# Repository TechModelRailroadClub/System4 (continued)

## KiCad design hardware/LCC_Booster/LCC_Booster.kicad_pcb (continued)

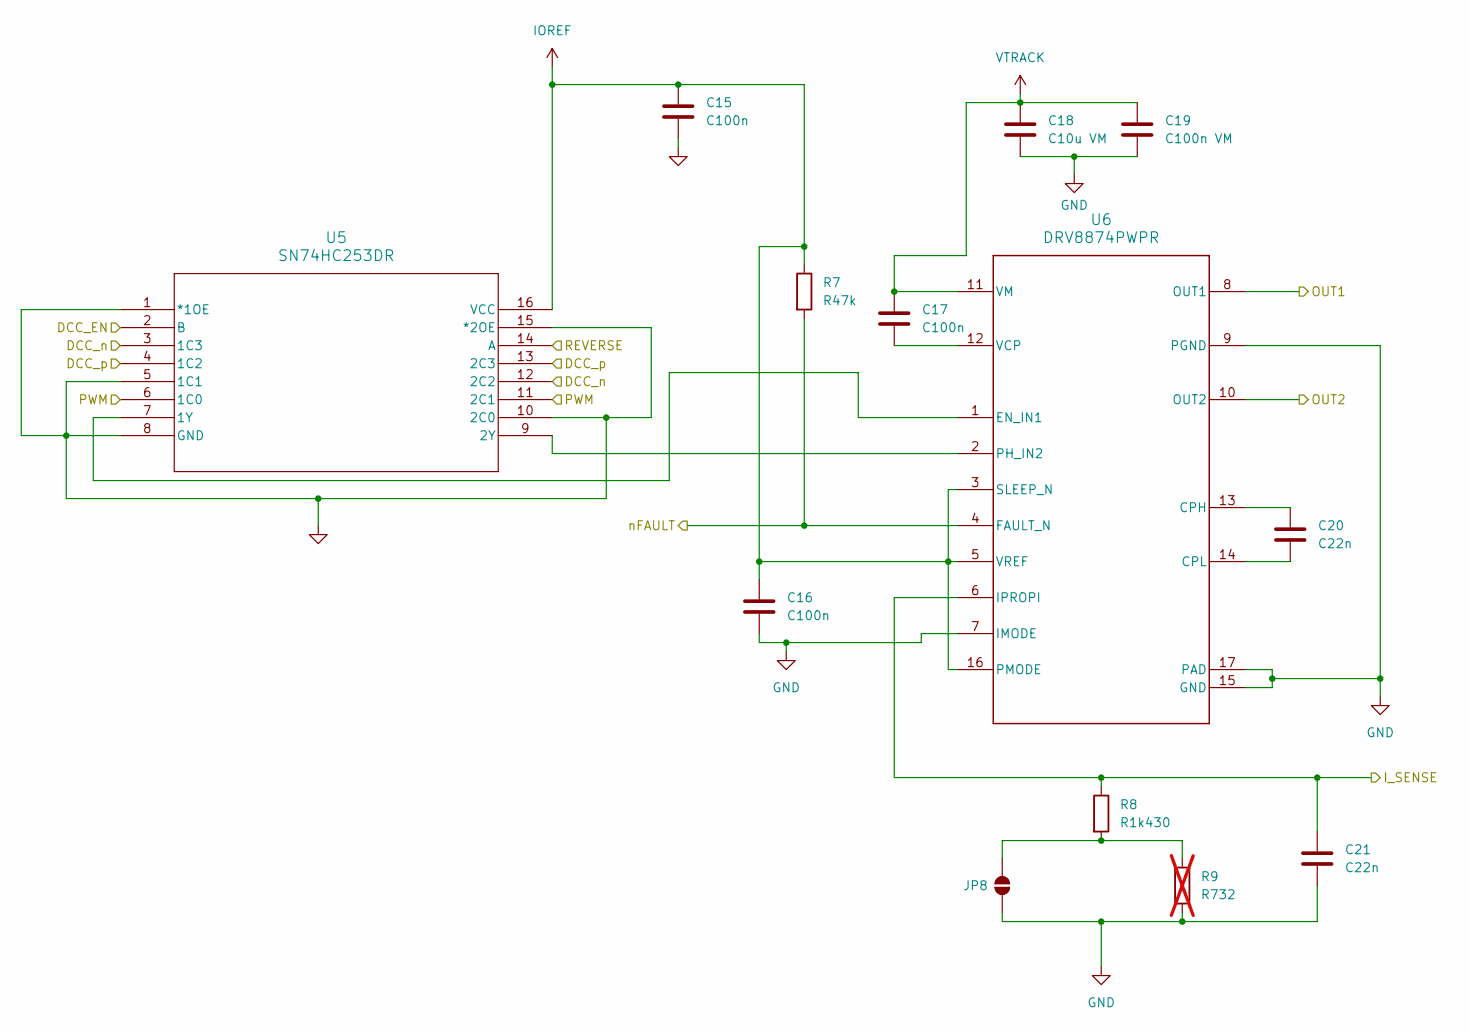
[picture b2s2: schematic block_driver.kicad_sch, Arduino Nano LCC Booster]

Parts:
C15, C16, C17: C100n; C_0805_2012Metric_Pad1.18x1.45mm_HandSolder; Manufacturer Part Number CL21B104KACNFNC
C18: C10u VM; C_1206_3216Metric_Pad1.33x1.80mm_HandSolder; Manufacturer Part Number CL31A106KBHNNNE
C19: C100n VM; C_0805_2012Metric_Pad1.18x1.45mm_HandSolder; Manufacturer Part Number CL21B104KBFXPJE
C20, C21: C22n; C_0805_2012Metric_Pad1.18x1.45mm_HandSolder; Manufacturer Part Number CL21B223JBANNNC
JP8: SolderJumper_2; SolderJumper-2_P1.3mm_Open_RoundedPad1.0x1.5mm
R7: R47k; R_0805_2012Metric_Pad1.20x1.40mm_HandSolder; Manufacturer Part Number ERJ6ENF4702V
R8: R1k430; R_0805_2012Metric_Pad1.20x1.40mm_HandSolder; Manufacturer Part Number RC0805FR-071K43L
R9: R732; R_0805_2012Metric_Pad1.20x1.40mm_HandSolder; not fitted
U5: SN74HC253DR; SO-16_3.9x9.9mm_P1.27mm; Manufacturer Part Number SN74HC253DR
U6: DRV8874PWPR; PWP0016J_NV; Manufacturer Part Number DRV8874PWPR

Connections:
/dcc_en_C: U5.2 (B); also elsewhere on the board
/dcc_n: U5.3 (1C3), U5.12 (2C2); also elsewhere on the board
/dcc_p: U5.4 (1C2), U5.13 (2C3); also elsewhere on the board
/dir_C: U5.14 (A); also elsewhere on the board
/nFault_C: R7.2, U6.4 (FAULT_N); also elsewhere on the board
/out1_C: U6.8 (OUT1); also elsewhere on the board
/out2_C: U6.10 (OUT2); also elsewhere on the board
/pwm_C: U5.6 (1C0), U5.11 (2C1); also elsewhere on the board
/sense_C: C21.1, R8.1, U6.6 (IPROPI); also elsewhere on the board
GND: C15.2, C16.2, C18.2, C19.2, C21.2, JP8.1 (A), R9.2, U5.1 (*1OE), U5.5 (1C1), U5.8 (GND), U5.10 (2C0), U5.15 (*2OE), U6.7 (IMODE), U6.9 (PGND), U6.15 (GND), U6.17 (PAD); also elsewhere on the board
IOREF: C15.1, C16.1, R7.1, U5.16 (VCC), U6.3 (SLEEP_N), U6.5 (VREF), U6.16 (PMODE); also elsewhere on the board
unnamed: JP8.2 (B), R8.2, R9.1
unnamed: U5.7 (1Y), U6.1 (EN_IN1)
unnamed: U5.9 (2Y), U6.2 (PH_IN2)
unnamed: C20.1, U6.13 (CPH)
unnamed: C20.2, U6.14 (CPL)
unnamed: C17.2, U6.12 (VCP)
VTRACK: C17.1, C18.1, C19.1, U6.11 (VM); also elsewhere on the board

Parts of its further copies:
C1, C2, C3, C10, C22, C23, C24: C100n; C_0805_2012Metric_Pad1.18x1.45mm_HandSolder; Manufacturer Part Number CL21B104KACNFNC
C4, C11, C25: C10u VM; C_1206_3216Metric_Pad1.33x1.80mm_HandSolder; Manufacturer Part Number CL31A106KBHNNNE
C5, C12: C100n VM; C_0805_2012Metric_Pad1.18x1.45mm_HandSolder; Manufacturer Part Number CL21B104KBFXPJE
C7, C13, C14, C27, C28: C22n; C_0805_2012Metric_Pad1.18x1.45mm_HandSolder; Manufacturer Part Number CL21B223JBANNNC
JP6, JP7, JP9: SolderJumper_2; SolderJumper-2_P1.3mm_Open_RoundedPad1.0x1.5mm
R1, R4: R47k; R_0805_2012Metric_Pad1.20x1.40mm_HandSolder; Manufacturer Part Number ERJ6ENF4702V
R2: R1k430; R_0805_2012Metric_Pad1.20x1.40mm_HandSolder; Manufacturer Part Number RC0805FR-071K43L
R3, R6, R12: R732; R_0805_2012Metric_Pad1.20x1.40mm_HandSolder; not fitted
U1, U3, U7: SN74HC253DR; SO-16_3.9x9.9mm_P1.27mm; Manufacturer Part Number SN74HC253DR
U2, U4, U8: DRV8874PWPR; PWP0016J_NV; Manufacturer Part Number DRV8874PWPR

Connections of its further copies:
/dcc_en_A: U1.2 (B); also elsewhere on the board
/dcc_en_B: U3.2 (B); also elsewhere on the board
/dcc_en_D: U7.2 (B); also elsewhere on the board
/dcc_n: U1.3 (1C3), U1.12 (2C2), U3.3 (1C3), U3.12 (2C2), U7.3 (1C3), U7.12 (2C2); also elsewhere on the board
/dcc_p: U1.4 (1C2), U1.13 (2C3), U3.4 (1C2), U3.13 (2C3), U7.4 (1C2), U7.13 (2C3); also elsewhere on the board
/dir_A: U1.14 (A); also elsewhere on the board
/dir_B: U3.14 (A); also elsewhere on the board
/dir_D: U7.14 (A); also elsewhere on the board
/nFault_A: R1.2, U2.4 (FAULT_N); also elsewhere on the board
/nFault_B: R4.2, U4.4 (FAULT_N); also elsewhere on the board
/nFault_C: U8.4 (FAULT_N); also elsewhere on the board
/out1_A: U2.8 (OUT1); also elsewhere on the board
/out1_B: U4.8 (OUT1); also elsewhere on the board
/out1_D: U8.8 (OUT1); also elsewhere on the board
/out2_A: U2.10 (OUT2); also elsewhere on the board
/out2_B: U4.10 (OUT2); also elsewhere on the board
/out2_D: U8.10 (OUT2); also elsewhere on the board
/pwm_A: U1.6 (1C0), U1.11 (2C1); also elsewhere on the board
/pwm_B: U3.6 (1C0), U3.11 (2C1); also elsewhere on the board
/pwm_D: U7.6 (1C0), U7.11 (2C1); also elsewhere on the board
/sense_A: C7.1, R2.1, U2.6 (IPROPI); also elsewhere on the board
/sense_B: C14.1, U4.6 (IPROPI); also elsewhere on the board
/sense_D: C28.1, U8.6 (IPROPI); also elsewhere on the board
GND: C1.2, C2.2, C4.2, C5.2, C7.2, C11.2, C12.2, C14.2, C22.2, C23.2, C25.2, C28.2, JP6.1 (A), JP7.1 (A), JP9.1 (A), R3.2, R6.2, R12.2, U1.1 (*1OE), U1.5 (1C1), U1.8 (GND), U1.10 (2C0), U1.15 (*2OE), U2.7 (IMODE), U2.9 (PGND), U2.15 (GND), U2.17 (PAD), U3.1 (*1OE), U3.5 (1C1), U3.8 (GND), U3.10 (2C0), U3.15 (*2OE), U4.7 (IMODE), U4.9 (PGND), U4.15 (GND), U4.17 (PAD), U7.1 (*1OE), U7.5 (1C1), U7.8 (GND), U7.10 (2C0), U7.15 (*2OE), U8.7 (IMODE), U8.9 (PGND), U8.15 (GND), U8.17 (PAD); also elsewhere on the board
IOREF: C1.1, C2.1, C22.1, C23.1, R1.1, R4.1, U1.16 (VCC), U2.3 (SLEEP_N), U2.5 (VREF), U2.16 (PMODE), U3.16 (VCC), U4.3 (SLEEP_N), U4.5 (VREF), U4.16 (PMODE), U7.16 (VCC), U8.3 (SLEEP_N), U8.5 (VREF), U8.16 (PMODE); also elsewhere on the board
unnamed: JP6.2 (B), R2.2, R3.1
unnamed 47: JP7.2 (B), R6.1; also elsewhere on the board
unnamed 49: JP9.2 (B), R12.1; also elsewhere on the board
unnamed: U1.7 (1Y), U2.1 (EN_IN1)
unnamed: U1.9 (2Y), U2.2 (PH_IN2)
unnamed 56: U2.13 (CPH); also elsewhere on the board
unnamed 57: U2.14 (CPL); also elsewhere on the board
unnamed: C3.2, U2.12 (VCP)
unnamed: U3.7 (1Y), U4.1 (EN_IN1)
unnamed: U3.9 (2Y), U4.2 (PH_IN2)
unnamed: C13.1, U4.13 (CPH)
unnamed: C13.2, U4.14 (CPL)
unnamed: C10.2, U4.12 (VCP)
unnamed: U7.7 (1Y), U8.1 (EN_IN1)
unnamed: U7.9 (2Y), U8.2 (PH_IN2)
unnamed: C27.1, U8.13 (CPH)
unnamed: C27.2, U8.14 (CPL)
unnamed: C24.2, U8.12 (VCP)
VTRACK: C3.1, C4.1, C5.1, C10.1, C11.1, C12.1, C24.1, C25.1, U2.11 (VM), U4.11 (VM), U8.11 (VM); also elsewhere on the board

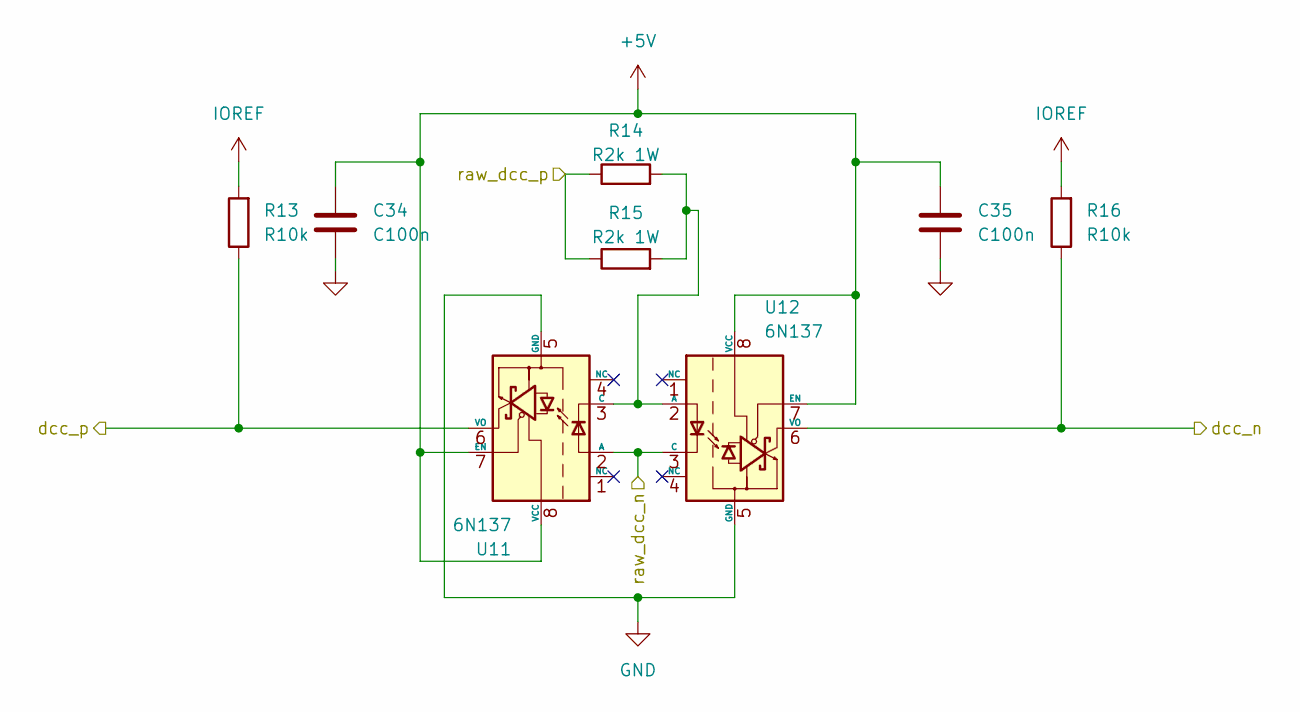
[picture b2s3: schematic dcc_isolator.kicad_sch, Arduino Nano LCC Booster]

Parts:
C34, C35: C100n; C_0805_2012Metric_Pad1.18x1.45mm_HandSolder; Manufacturer Part Number CL21B104KACNFNC
R13, R16: R10k; R_0805_2012Metric_Pad1.20x1.40mm_HandSolder; Manufacturer Part Number RC0805JR-0710KL
R14, R15: R2k 1W; R_2512_6332Metric_Pad1.40x3.35mm_HandSolder; Manufacturer Part Number AC2512JK-072KL
U11, U12: 6N137; DIP-8_W7.62mm_SMDSocket_SmallPads; Manufacturer Part Number 6N137S-TA1-L

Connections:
+5V: C34.1, C35.1, U11.7 (EN), U11.8 (VCC), U12.7 (EN), U12.8 (VCC); also elsewhere on the board
/dcc_n: R16.1, U12.6 (VO); also elsewhere on the board
/dcc_p: R13.1, U11.6 (VO); also elsewhere on the board
/raw_dcc_n: U11.2 (A), U12.3 (C); also elsewhere on the board
/raw_dcc_p: R14.1, R15.1; also elsewhere on the board
GND: C34.2, C35.2, U11.5 (GND), U12.5 (GND); also elsewhere on the board
IOREF: R13.2, R16.2; also elsewhere on the board
unnamed: R14.2, R15.2, U11.3 (C), U12.2 (A)

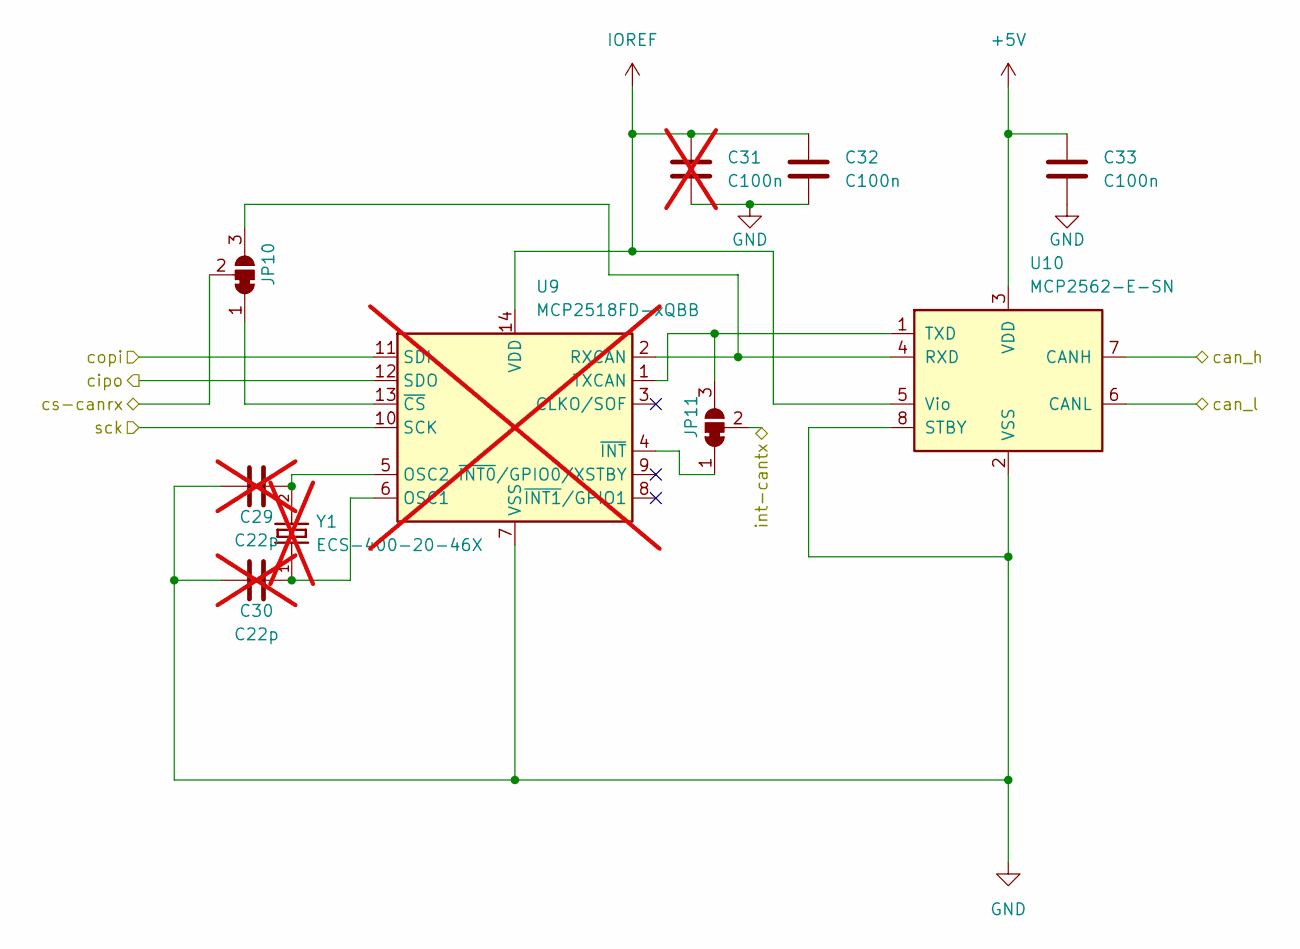
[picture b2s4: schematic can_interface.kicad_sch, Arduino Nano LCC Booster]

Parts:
C29, C30: C22p; C_0805_2012Metric_Pad1.18x1.45mm_HandSolder; not fitted
C31: C100n; C_0805_2012Metric_Pad1.18x1.45mm_HandSolder; not fitted
C32, C33: C100n; C_0805_2012Metric_Pad1.18x1.45mm_HandSolder; Manufacturer Part Number CL21B104KACNFNC
JP10, JP11: SolderJumper_3_Bridged12; SolderJumper-3_P1.3mm_Bridged12_RoundedPad1.0x1.5mm_NumberL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
U9: MCP2518FD-xQBB; SOIC-14_3.9x8.7mm_P1.27mm; not fitted
U10: MCP2562-E-SN; SOIC-8_3.9x4.9mm_P1.27mm; Manufacturer Part Number MCP2562-E-SN
Y1: ECS-400-20-46X; XTAL_ECS-400-20-46X; not fitted

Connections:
+5V: C33.1, U10.3 (VDD); also elsewhere on the board
/can_h: U10.7 (CANH); also elsewhere on the board
/can_l: U10.6 (CANL); also elsewhere on the board
/cipo-nFault_B: U9.12 (SDO); also elsewhere on the board
/copi-nFault_A: U9.11 (SDI); also elsewhere on the board
/cs-canrx: JP10.2 (C); also elsewhere on the board
/int-cantx: JP11.2 (C); also elsewhere on the board
/sck-nFault_CD: U9.10 (SCK); also elsewhere on the board
GND: C29.1, C30.1, C31.2, C32.2, C33.2, U9.7 (VSS), U9.15 (VSS), U10.2 (VSS), U10.8 (STBY); also elsewhere on the board
IOREF: C31.1, C32.1, U9.14 (VDD), U10.5 (Vio); also elsewhere on the board
unnamed: JP10.1 (A), U9.13 (~CS)
unnamed: JP10.3 (B), U9.2 (RXCAN), U10.4 (RXD)
unnamed: JP11.1 (A), U9.4 (~INT)
unnamed: JP11.3 (B), U9.1 (TXCAN), U10.1 (TXD)
unnamed: C30.2, U9.6 (OSC1), Y1.1
unnamed: C29.2, U9.5 (OSC2), Y1.2

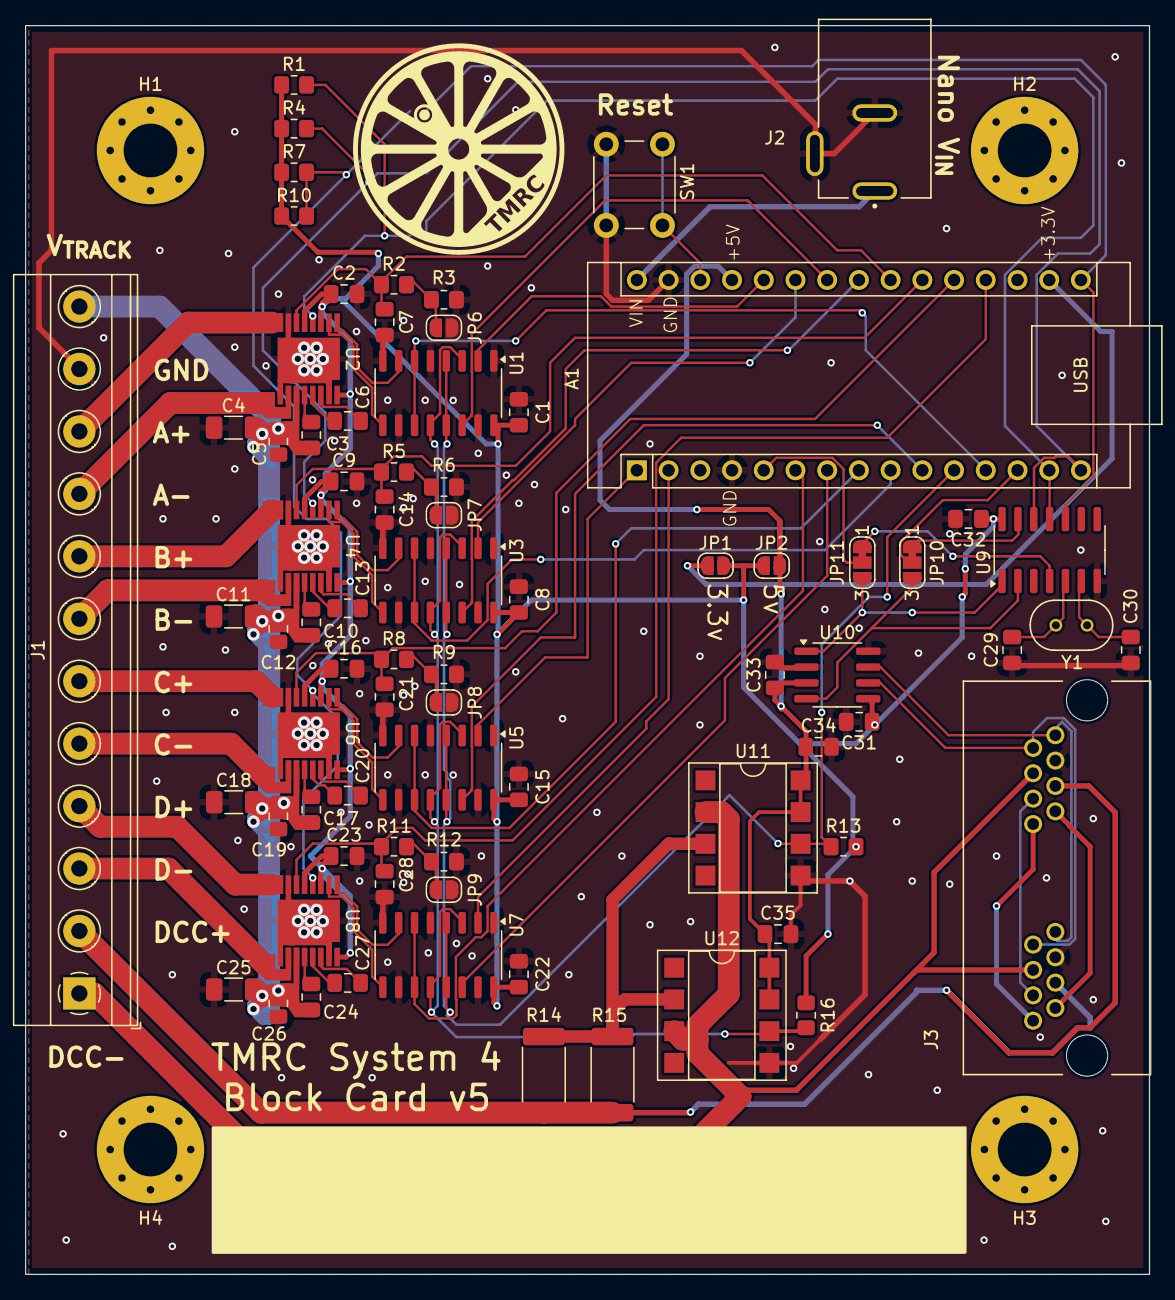
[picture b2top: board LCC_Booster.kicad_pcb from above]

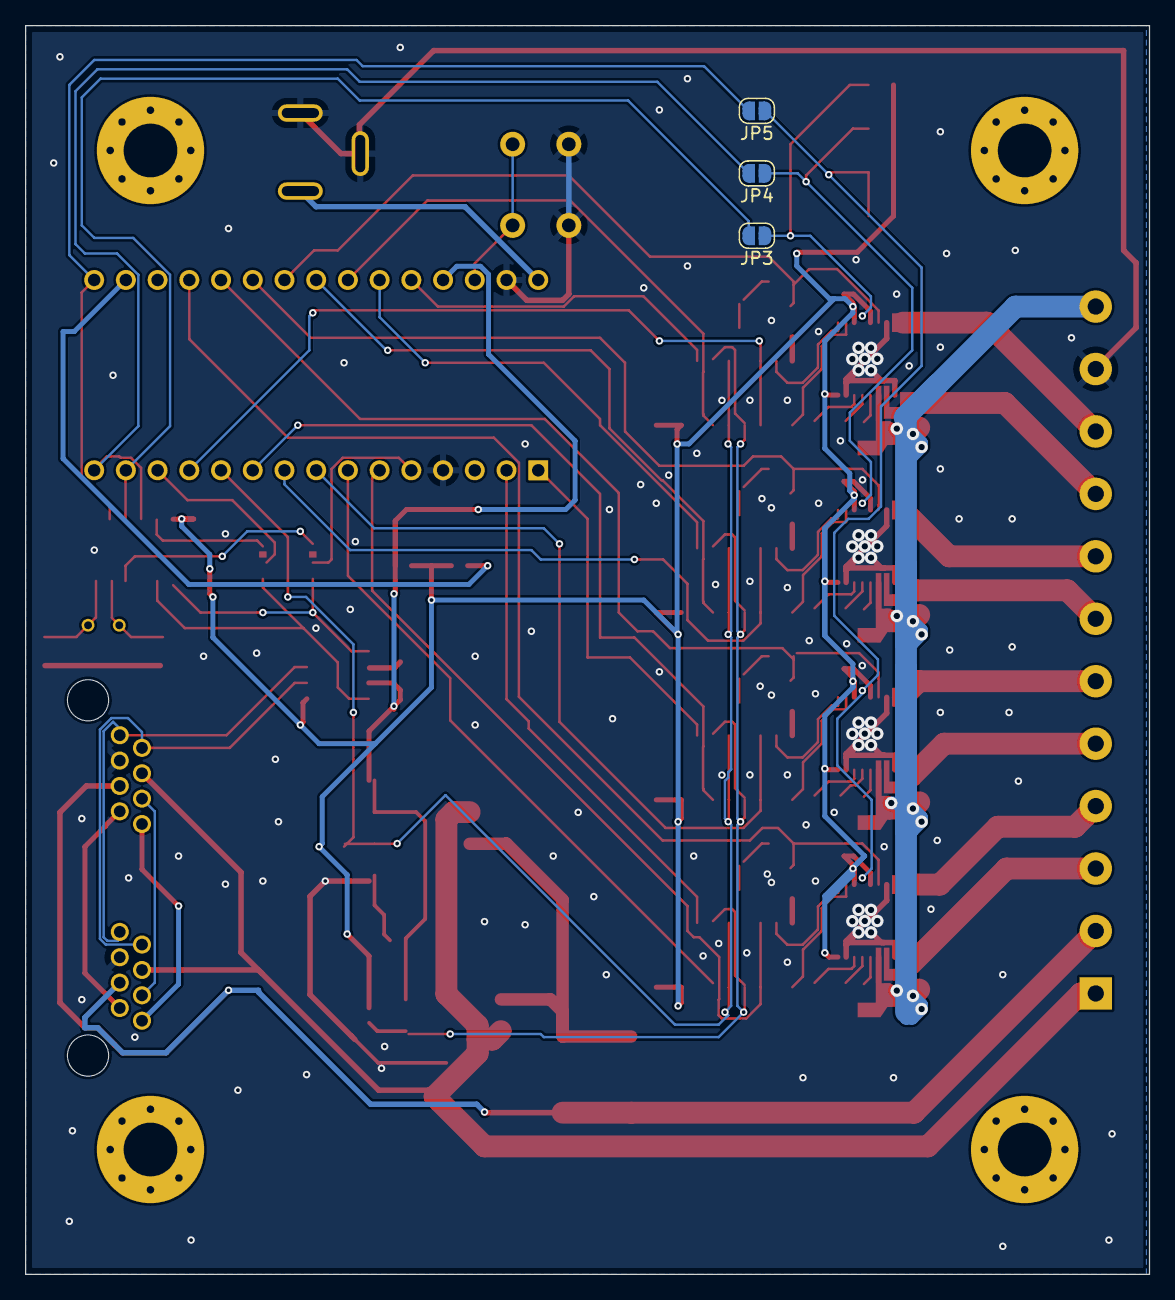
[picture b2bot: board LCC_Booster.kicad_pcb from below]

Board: 2 copper layers, 90.0 x 100.0 mm, 84 parts (3 on the bottom side), 79 nets.

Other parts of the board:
C6: C22n; C_0805_2012Metric_Pad1.18x1.45mm_HandSolder
C8, C9: C100n; C_0805_2012Metric_Pad1.18x1.45mm_HandSolder
C26: C100n VM; C_0805_2012Metric_Pad1.18x1.45mm_HandSolder
R5, R11: R1k430; R_0805_2012Metric_Pad1.20x1.40mm_HandSolder
R10: R47k; R_0805_2012Metric_Pad1.20x1.40mm_HandSolder

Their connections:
/nFault_C: R10.2; also elsewhere on the board
/sense_B: R5.1; also elsewhere on the board
/sense_D: R11.1; also elsewhere on the board
GND: C8.2, C9.2, C26.2; also elsewhere on the board
IOREF: C8.1, C9.1, R10.1; also elsewhere on the board
unnamed 47: R5.2; also elsewhere on the board
unnamed 49: R11.2; also elsewhere on the board
unnamed 56: C6.1; also elsewhere on the board
unnamed 57: C6.2; also elsewhere on the board
VTRACK: C26.1; also elsewhere on the board

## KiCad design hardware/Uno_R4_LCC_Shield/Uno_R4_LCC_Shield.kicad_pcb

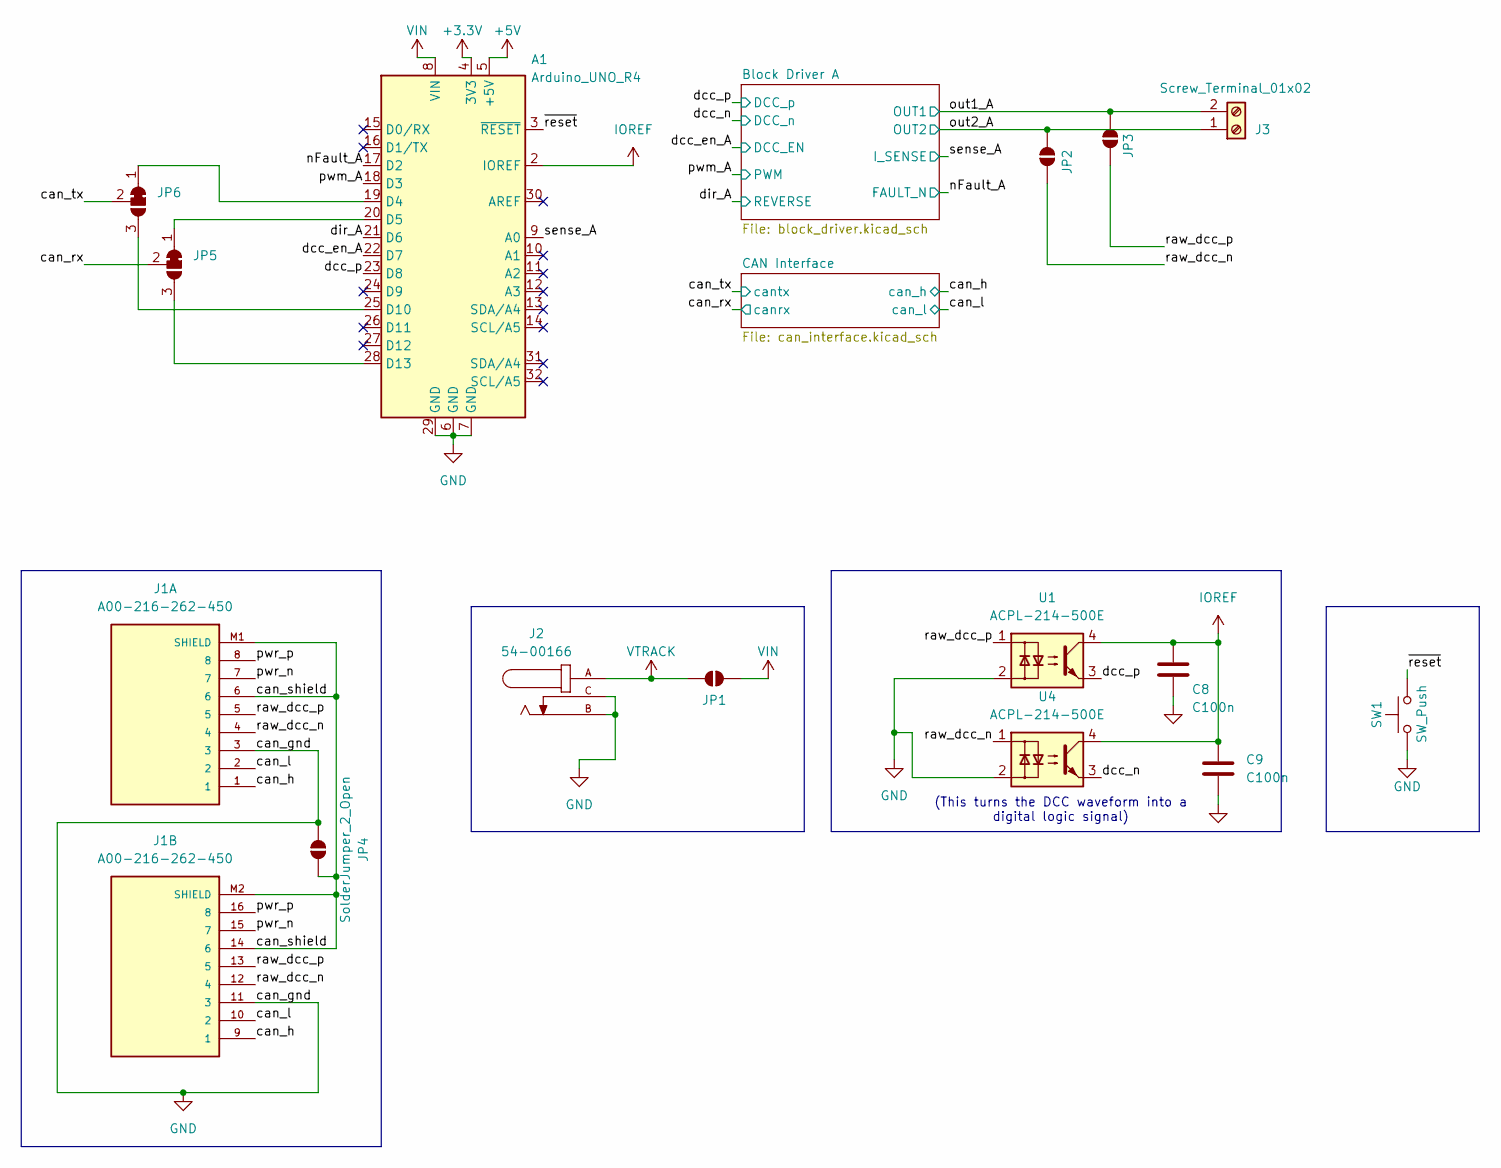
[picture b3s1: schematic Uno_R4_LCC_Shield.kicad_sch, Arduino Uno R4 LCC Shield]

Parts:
A1: Arduino_UNO_R4; Uno_Shield
C8, C9: C100n; C_0402_1005Metric_Pad0.74x0.62mm_HandSolder
J1: A00-216-262-450; EDAC_A00-216-262-450
J2: 54-00166; TENSILITY_54-00166; PARTREV A
J3: Screw_Terminal_01x02; TerminalBlock_Phoenix_MKDS-1,5-2_1x02_P5.00mm_Horizontal
JP1, JP2, JP3, JP4: SolderJumper_2_Open; SolderJumper-2_P1.3mm_Open_RoundedPad1.0x1.5mm
JP5, JP6: SolderJumper_3_Bridged12; SolderJumper-3_P1.3mm_Bridged12_RoundedPad1.0x1.5mm
SW1: SW_Push; SW_PUSH_6mm_H4.3mm
U1, U4: ACPL-214-500E; SOP-4_4.4x2.6mm_P1.27mm

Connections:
+3.3V: A1.4 (3V3)
+5V: A1.5 (+5V); also elsewhere on the board
/can_h: J1.1, J1.9 (1); also elsewhere on the board
/can_l: J1.2, J1.10 (2); also elsewhere on the board
/can_rx: JP5.2 (C); also elsewhere on the board
/can_shield: J1.6, J1.14 (6), J1.M1 (SHIELD), J1.M2 (SHIELD), JP4.1 (A)
/can_tx: JP6.2 (C); also elsewhere on the board
/dcc_en_A: A1.22 (D7); also elsewhere on the board
/dcc_n: U4.3; also elsewhere on the board
/dcc_p: A1.23 (D8), U1.3; also elsewhere on the board
/dir_A: A1.21 (D6); also elsewhere on the board
/nFault_A: A1.17 (D2); also elsewhere on the board
/out1_A: J3.2, JP3.2 (B); also elsewhere on the board
/out2_A: J3.1, JP2.2 (B); also elsewhere on the board
/pwm_A: A1.18 (D3); also elsewhere on the board
/pwr_n: J1.7, J1.15 (7)
/pwr_p: J1.8, J1.16 (8)
/raw_dcc_n: J1.4, J1.12 (4), JP2.1 (A), U4.1
/raw_dcc_p: J1.5, J1.13 (5), JP3.1 (A), U1.1
/sense_A: A1.9 (A0); also elsewhere on the board
/~reset: A1.3 (~RESET), SW1.2
GND: A1.6 (GND), A1.7 (GND), A1.29 (GND), C8.2, C9.2, J1.3, J1.11 (3), J2.B, J2.C, JP4.2 (B), SW1.1, U1.2, U4.2; also elsewhere on the board
IOREF: A1.2 (IOREF), C8.1, C9.1, U1.4, U4.4; also elsewhere on the board
unnamed: A1.19 (D4), JP6.1 (A)
unnamed: A1.20 (D5), JP5.1 (A)
unnamed: A1.25 (D10), JP6.3 (B)
unnamed: A1.28 (D13), JP5.3 (B)
VIN: A1.8 (VIN), JP1.2 (B)
VTRACK: J2.A, JP1.1 (A); also elsewhere on the board

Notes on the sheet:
(This turns the DCC waveform into a digital logic signal)

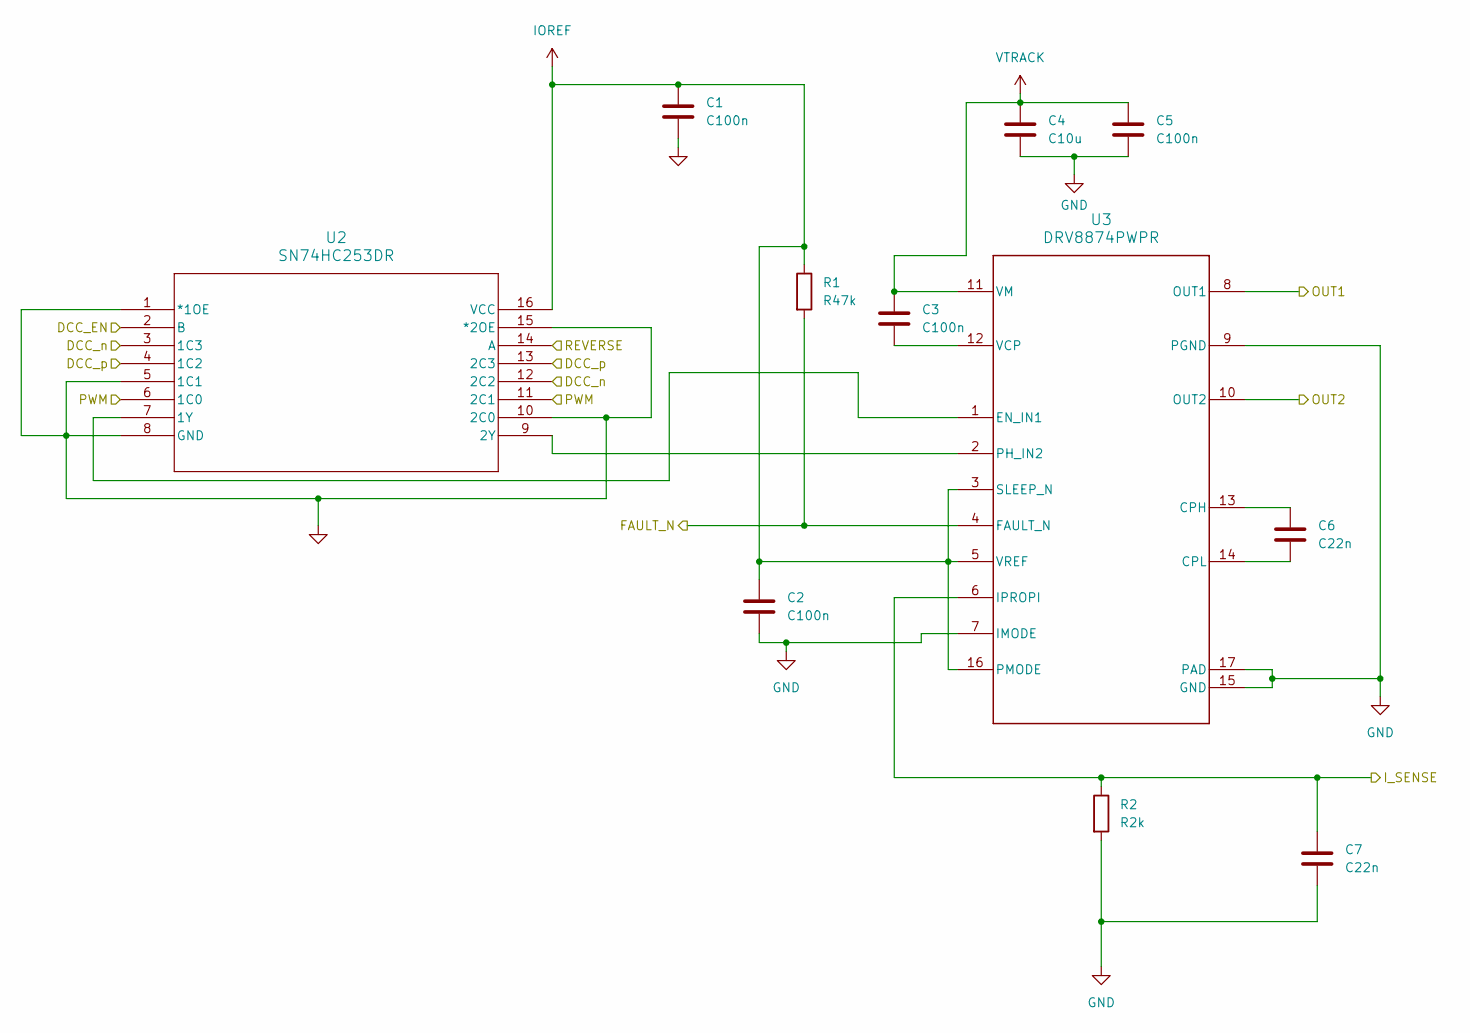
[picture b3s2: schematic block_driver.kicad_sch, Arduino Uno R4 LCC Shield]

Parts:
C1, C2, C3, C5: C100n; C_0402_1005Metric_Pad0.74x0.62mm_HandSolder
C4: C10u; C_1206_3216Metric_Pad1.33x1.80mm_HandSolder
C6, C7: C22n; C_0402_1005Metric_Pad0.74x0.62mm_HandSolder
R1: R47k; R_01005_0402Metric_Pad0.57x0.30mm_HandSolder
R2: R2k; R_01005_0402Metric_Pad0.57x0.30mm_HandSolder
U2: SN74HC253DR; SO-16_3.9x9.9mm_P1.27mm
U3: DRV8874PWPR; PWP0016J_NV

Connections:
/dcc_en_A: U2.2 (B); also elsewhere on the board
/dcc_n: U2.3 (1C3), U2.12 (2C2); also elsewhere on the board
/dcc_p: U2.4 (1C2), U2.13 (2C3); also elsewhere on the board
/dir_A: U2.14 (A); also elsewhere on the board
/nFault_A: R1.2, U3.4 (FAULT_N); also elsewhere on the board
/out1_A: U3.8 (OUT1); also elsewhere on the board
/out2_A: U3.10 (OUT2); also elsewhere on the board
/pwm_A: U2.6 (1C0), U2.11 (2C1); also elsewhere on the board
/sense_A: C7.1, R2.1, U3.6 (IPROPI); also elsewhere on the board
GND: C1.2, C2.2, C4.2, C5.2, C7.2, R2.2, U2.1 (*1OE), U2.5 (1C1), U2.8 (GND), U2.10 (2C0), U2.15 (*2OE), U3.7 (IMODE), U3.9 (PGND), U3.15 (GND), U3.17 (PAD); also elsewhere on the board
IOREF: C1.1, C2.1, R1.1, U2.16 (VCC), U3.3 (SLEEP_N), U3.5 (VREF), U3.16 (PMODE); also elsewhere on the board
unnamed: U2.7 (1Y), U3.1 (EN_IN1)
unnamed: U2.9 (2Y), U3.2 (PH_IN2)
unnamed: C6.1, U3.13 (CPH)
unnamed: C6.2, U3.14 (CPL)
unnamed: C3.2, U3.12 (VCP)
VTRACK: C3.1, C4.1, C5.1, U3.11 (VM); also elsewhere on the board

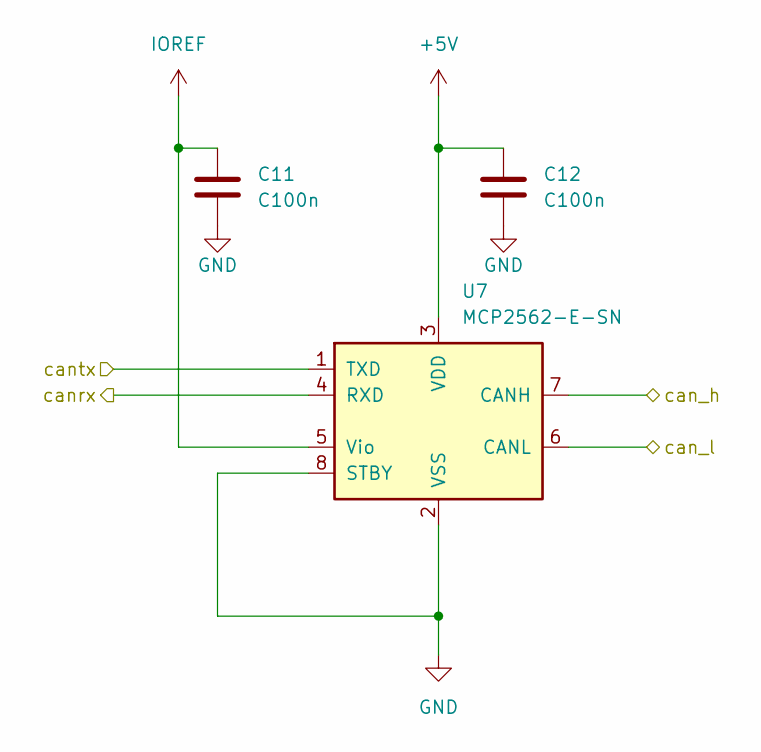
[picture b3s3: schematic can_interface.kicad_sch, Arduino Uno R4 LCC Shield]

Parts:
C11, C12: C100n; C_0402_1005Metric_Pad0.74x0.62mm_HandSolder
U7: MCP2562-E-SN; SOIC-8_3.9x4.9mm_P1.27mm

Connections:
+5V: C12.1, U7.3 (VDD); also elsewhere on the board
/can_h: U7.7 (CANH); also elsewhere on the board
/can_l: U7.6 (CANL); also elsewhere on the board
/can_rx: U7.4 (RXD); also elsewhere on the board
/can_tx: U7.1 (TXD); also elsewhere on the board
GND: C11.2, C12.2, U7.2 (VSS), U7.8 (STBY); also elsewhere on the board
IOREF: C11.1, U7.5 (Vio); also elsewhere on the board

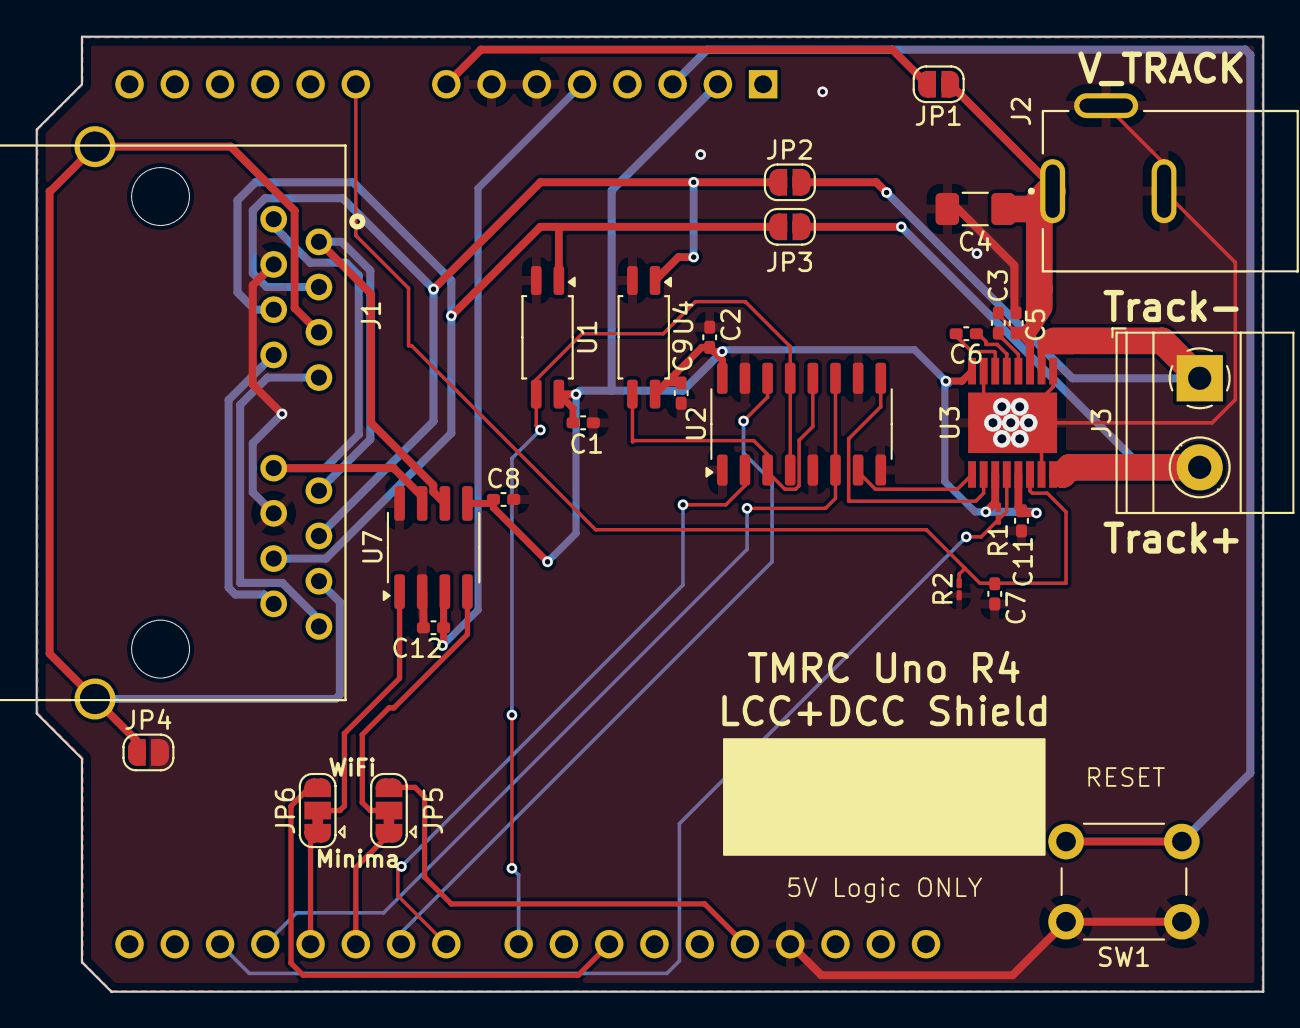
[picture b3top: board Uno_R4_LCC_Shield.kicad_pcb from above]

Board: 2 copper layers, 68.8 x 53.6 mm, 29 parts (1 on the bottom side), 33 nets.
